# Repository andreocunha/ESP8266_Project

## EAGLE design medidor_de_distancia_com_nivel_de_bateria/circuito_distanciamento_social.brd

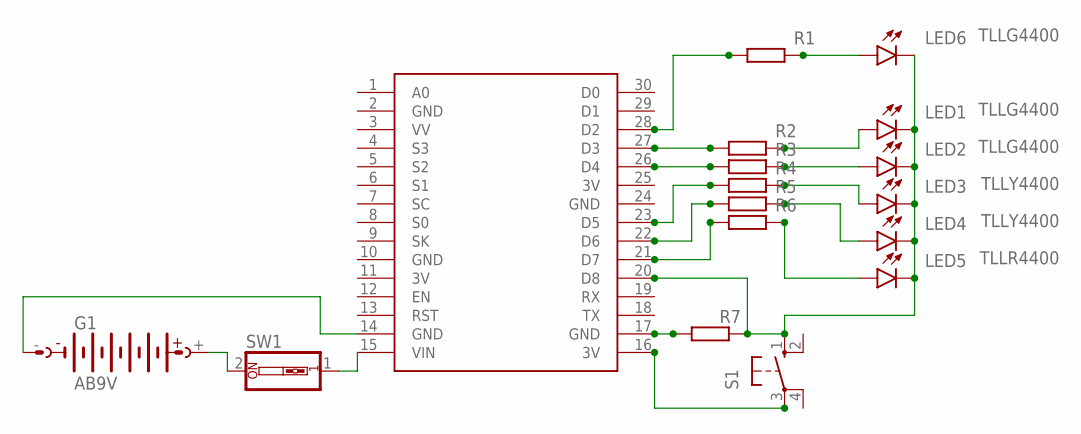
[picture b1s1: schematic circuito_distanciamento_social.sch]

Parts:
G1: AB9V
LED1, LED2, LED6: TLLG4400; LED3MM
LED3, LED4: TLLY4400; LED3MM
LED5: TLLR4400; LED3MM
R1, R2, R3, R4, R5, R6, R7: R-EU_0207/10; 0207/10
S1: 10-XX; B3F-10XX
SW1: SW_DIP-1; EDG-01
U$1: NODEMCU

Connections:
3V: U$1.11 (3V), U$1.25 (3V)
GND: U$1.2 (GND), U$1.10 (GND), U$1.24 (GND)
unnamed: R1.1, U$1.28 (D2)
unnamed: LED1.K (C), LED2.K (C), LED3.K (C), LED4.K (C), LED5.K (C), LED6.K (C), R7.2, S1.1 (S), U$1.20 (D8)
unnamed: R2.1, U$1.27 (D3)
unnamed: R3.1, U$1.26 (D4)
unnamed: R4.1, U$1.23 (D5)
unnamed: R5.1, U$1.22 (D6)
unnamed: R6.1, U$1.21 (D7)
unnamed: LED1.A, R2.2
unnamed: LED6.A, R1.2
unnamed: LED2.A, R3.2
unnamed: LED3.A, R4.2
unnamed: LED5.A, R6.2
unnamed: LED4.A, R5.2
unnamed: R7.1, U$1.17 (GND)
unnamed: G1.+, SW1.2
unnamed: S1.3, U$1.16 (3V)
unnamed: G1.-, U$1.14 (GND)
unnamed: SW1.1, U$1.15 (VIN)

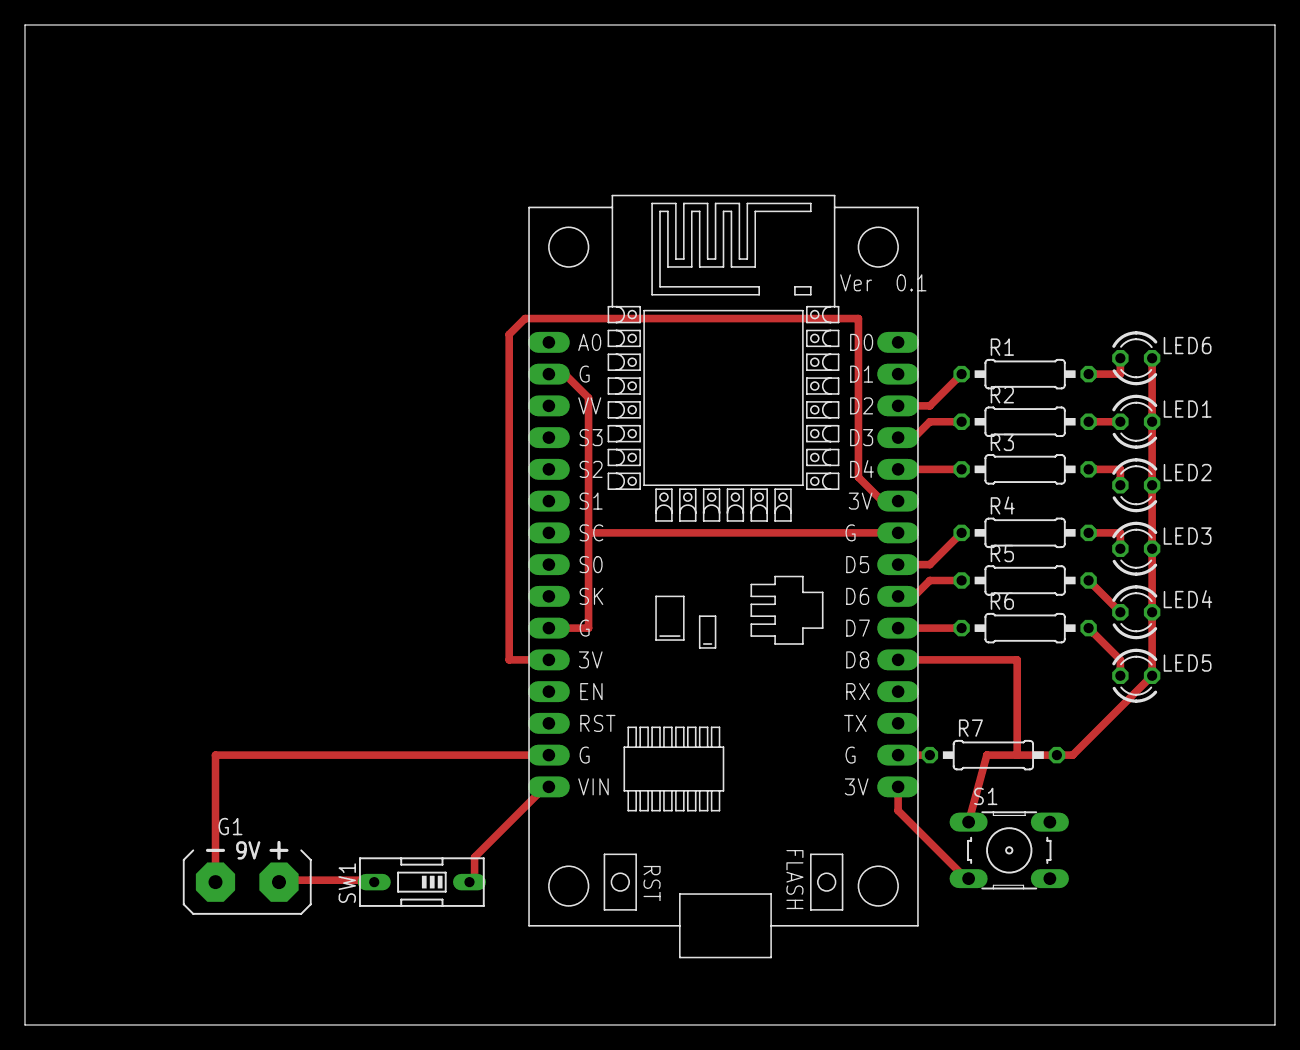
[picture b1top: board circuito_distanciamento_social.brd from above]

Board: 2 copper layers, 100.0 x 80.0 mm, 17 parts (0 on the bottom side), 20 nets.

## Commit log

2020-05-30 Configurando Esp8266 como ponto de acesso
2020-05-30 Medidor de distanciamento social
2020-05-30 Medidor de potencia do sinal wifi
2020-05-30 Medidor de distanciamento Social c/ software 3D
2020-08-20 Escaneia wifi em um canal específico
